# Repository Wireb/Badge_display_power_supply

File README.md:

# Badge display power supply
This design is a dual 6V to 18V input to settable 1.5A output switching regulator supply.   
Main purpose is to power up conference badges in display cases.   
  
The output voltage is set by R8 and R10. Pick the proper resistor value based on the table below:

|Rx|output V|Typical use|
| --- | --- | --- |
|7.68k|5V|USB powered|
|8.66k|4.5V|3x AA/AAA replacement|
|13k|3.3V|LiPo replacement mid charge|
|14.7k|3V|coin cell or 2x AA/AAA replacement|

**NOTE you MUST remove the battery when using this design as a battery replacement!**

J1, J2, and J3 are supply side input / output jacks. Cards are designed to be daisy chained between display using 5.5x2.5mm cables  
J4, J5, J6, J7, and J8 are output 1 controlled by R8  
J9, J10, J11, J12, and J13 are output 2 controlled by R10  
Populate connectors based on your needs.  

Thinking about making a smaller / cheaper single reg version as well in the future. 

## KiCad
This is a KiCad 5.0 project. 

## documentation
This is a XLS/PDF dump of the spreadsheet documentation I was using during development. 

## OSHpark PCBs
PCB design can be found here:
https://www.oshpark.com/shared_projects/n03EZh99

Copyright (c) 2018 Peter Shabino

Permission is hereby granted, free of charge, to any person obtaining a copy of this hardware, software, and associated documentation files 
(the "Product"), to deal in the Product without restriction, including without limitation the rights to use, copy, modify, merge, publish, 
distribute, sublicense, and/or sell copies of the Product, and to permit persons to whom the Product is furnished to do so, subject to the 
following conditions:

The above copyright notice and this permission notice shall be included in all copies or substantial portions of the Product.

THE PRODUCT IS PROVIDED "AS IS", WITHOUT WARRANTY OF ANY KIND, EXPRESS OR IMPLIED, INCLUDING BUT NOT LIMITED TO THE WARRANTIES OF 
MERCHANTABILITY, FITNESS FOR A PARTICULAR PURPOSE AND NONINFRINGEMENT. IN NO EVENT SHALL THE AUTHORS OR COPYRIGHT HOLDERS BE LIABLE 
FOR ANY CLAIM, DAMAGES OR OTHER LIABILITY, WHETHER IN AN ACTION OF CONTRACT, TORT OR OTHERWISE, ARISING FROM, OUT OF OR IN CONNECTION 
WITH THE PRODUCT OR THE USE OR OTHER DEALINGS IN THE PRODUCT.

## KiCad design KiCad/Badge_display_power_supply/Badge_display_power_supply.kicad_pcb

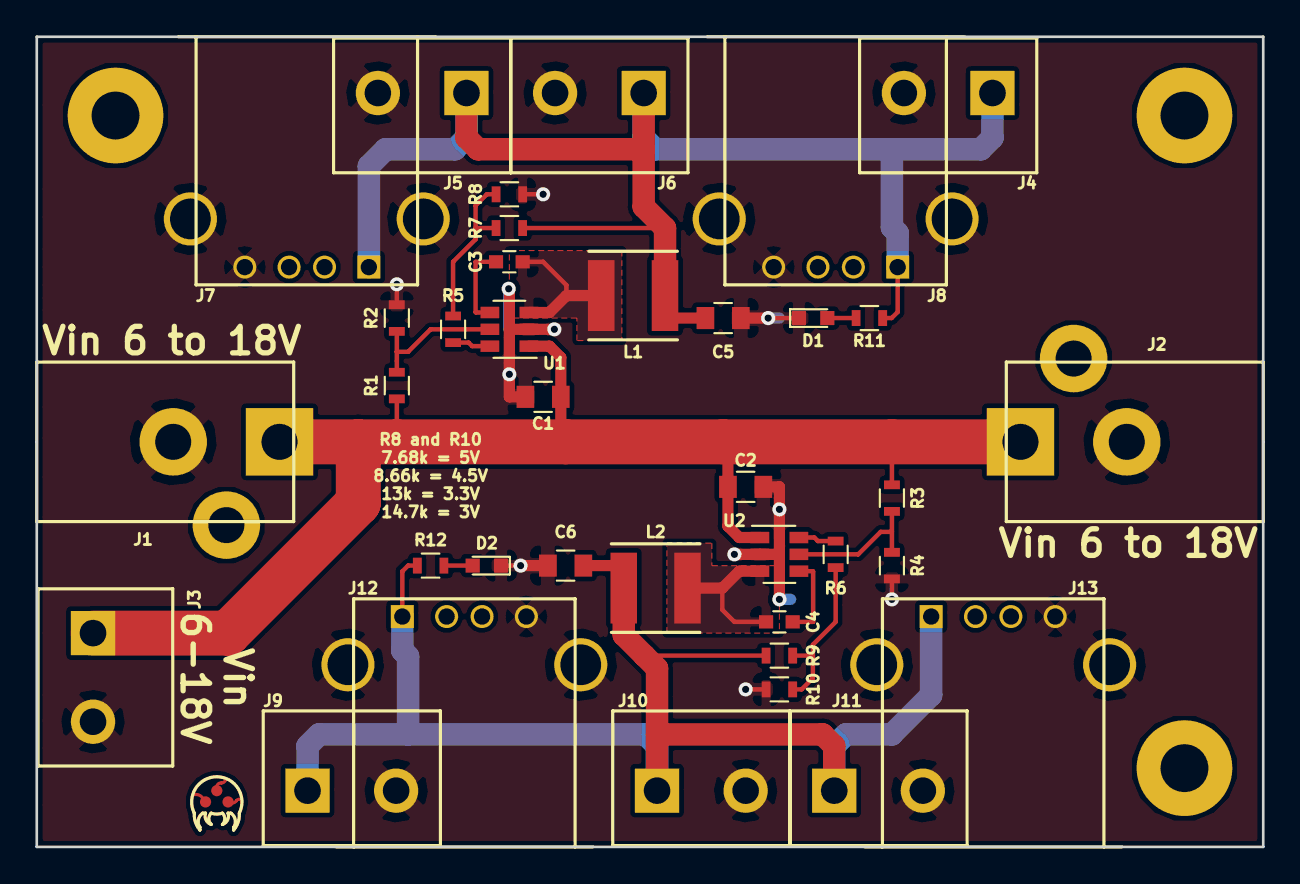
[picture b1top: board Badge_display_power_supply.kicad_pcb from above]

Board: 2 copper layers, 69.2 x 45.7 mm, 38 parts (0 on the bottom side), 16 nets.

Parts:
C1, C2, C5, C6: 22uF; C_0805
C3, C4: 1uF; C_0603
D1, D2: LED_red; LED_0603
J1, J2: PJ-102BH; CUI_PJ-102BH
J3, J4, J5, J6, J9, J10, J11: Screw; DG301-5.002P-12
J7, J8, J12, J13: SS-52100-001; Stewart_USB_SS-52100-001
L1, L2: 6.5uH; Yuden_Inductor_4.9x4.9
R1, R3: 499k; R_0603
R2, R4: 100k; R_0603
R5, R6: 59k; R_0603
R7, R9: 40.2k; R_0603
R8, R10: 7.68k; R_0603
R11, R12: 499; R_0603
U1, U2: AP65111; SOT-23-6
icon1: Metroid; metroid

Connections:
GND: C1.2, C2.2, C5.2, C6.2, D1.1, D2.1, J1.2, J2.2, J3.2, J4.2, J5.2, J6.2, J7.4, J7.5, J8.4, J8.5, J9.2, J10.2, J11.2, J12.4, J12.5, J13.4, J13.5, R2.2, R4.2, R8.2, R10.2, U1.2, U2.2
unnamed: C1.1, C2.1, J1.1, J2.1, J3.1, R1.1, R3.1, U1.1, U2.1
unnamed: C3.1, L1.2, U1.3
unnamed: C3.2, U1.4
unnamed: C4.1, L2.2, U2.3
unnamed: C4.2, U2.4
unnamed: C5.1, J4.1, J5.1, J6.1, J7.1, J8.1, L1.1, R7.1, R11.1
unnamed: C6.1, J9.1, J10.1, J11.1, J12.1, J13.1, L2.1, R9.1, R12.1
unnamed: D1.2, R11.2
unnamed: D2.2, R12.2
unnamed: R1.2, R2.1, U1.5
unnamed: R3.2, R4.1, U2.5
unnamed: R5.1, R7.2, R8.1
unnamed: R5.2, U1.6
unnamed: R6.2, U2.6
unnamed: R6.1, R9.2, R10.1

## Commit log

2018-09-09 :space_invader: Added .gitattributes & .gitignore files
2018-09-09 First post
    Protos delivered and work.
2018-09-09 readme updates
2018-09-09 updates in readme

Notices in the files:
KiCad/Badge_display_power_supply/Badge_display_power_supply.kicad_pcb:
PJS 20Aug2018 MIT License.
